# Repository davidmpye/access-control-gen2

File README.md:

This repo contains the Controllers (firmware, pcb design, printables) that make up part of the Makerspace Access Control System.

The basic principles they follow are:

* Use NFC readers (enrol a fob or card of your choice)
* Receive updates over Wifi, but cached on the controller in flash storage.
* Able to work offline and queue events to send to controller when connectivity established
* Provide log updates to the access controller backend to allow device usage to be logged and tracked.

They're an important part of our Health and Safety obligations to our members, ensuring that only authorised users are able to use (potentially) dangerous hardware.

The documentation is on the [wiki (in progress...!)](https://github.com/MakerSpaceNewcastle/access-control-gen2/wiki)

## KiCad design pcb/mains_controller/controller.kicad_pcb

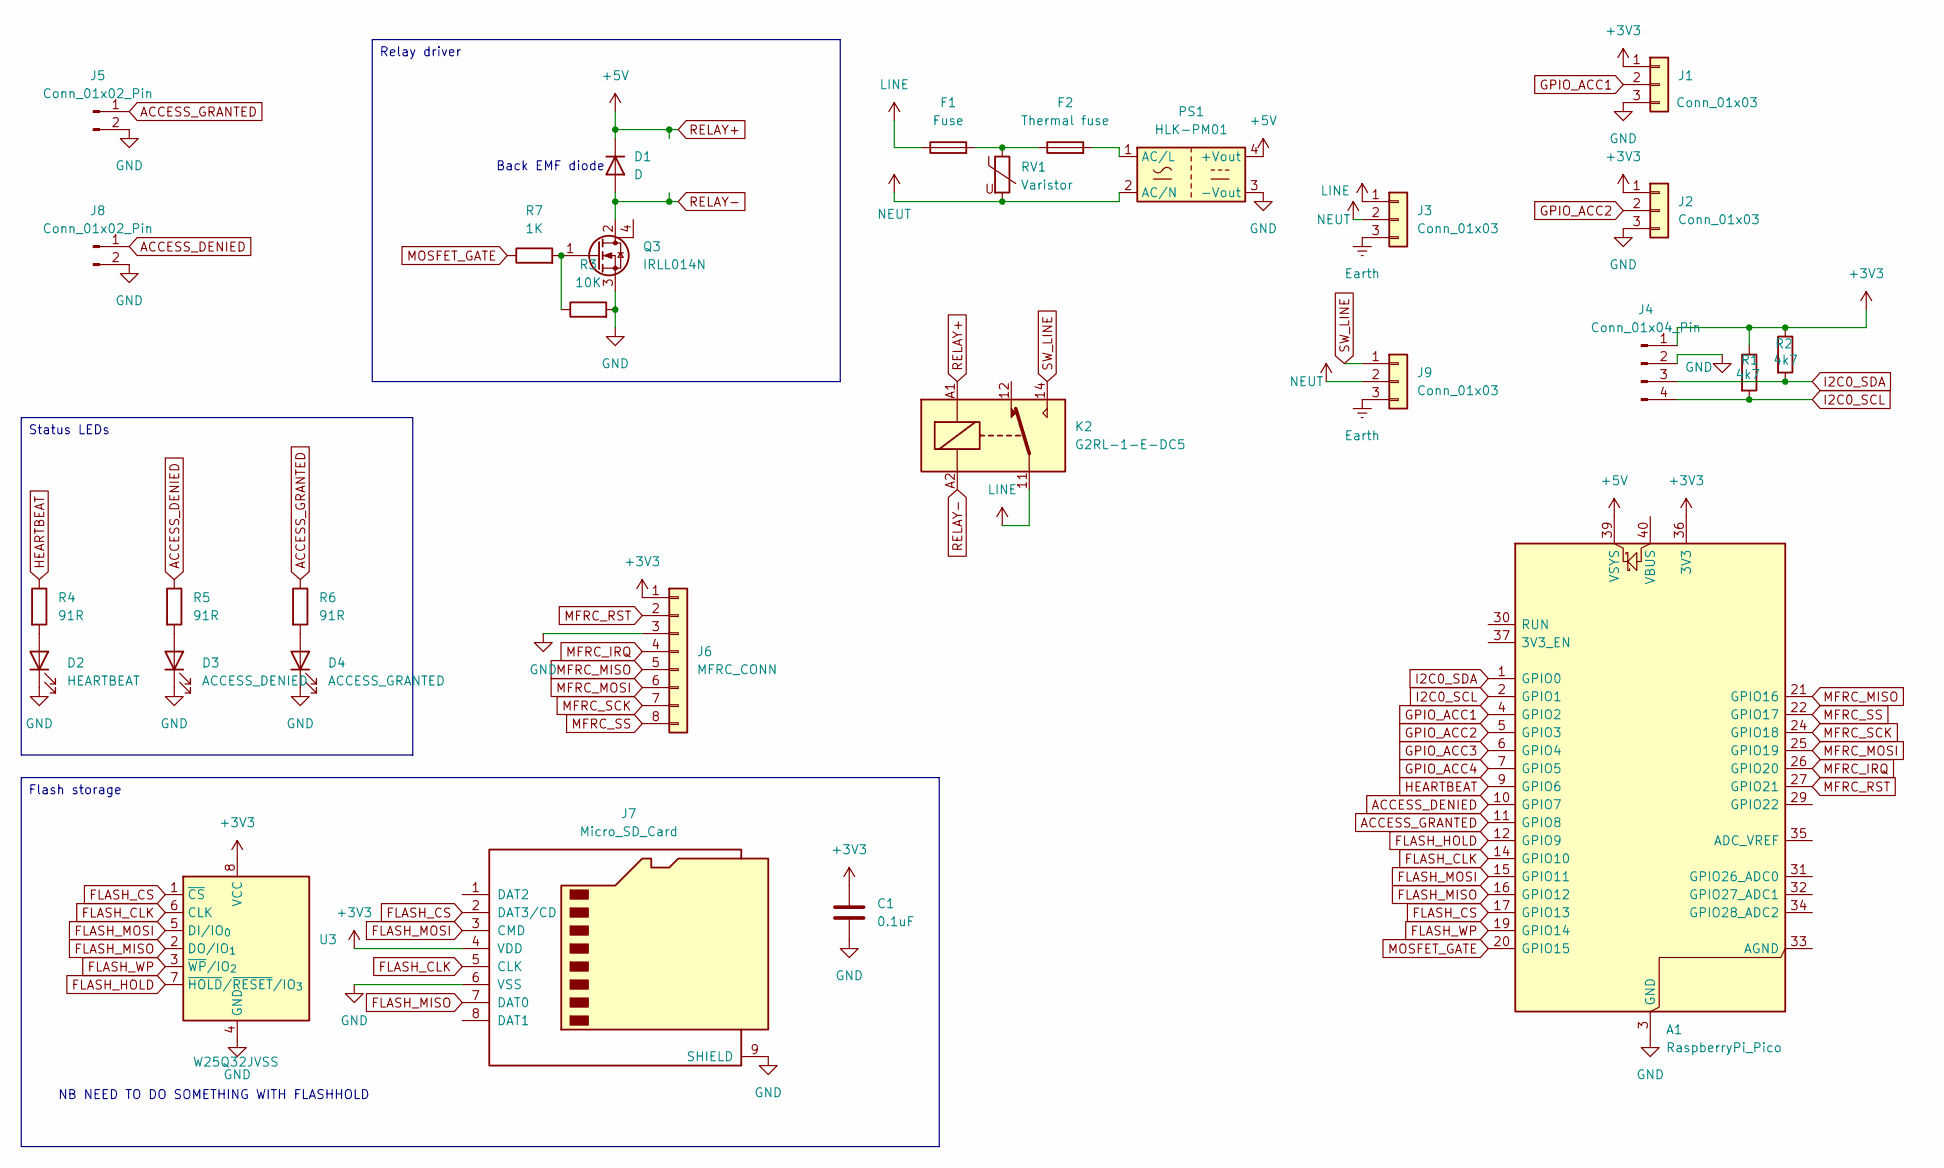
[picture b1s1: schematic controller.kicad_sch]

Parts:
A1: RaspberryPi_Pico; RaspberryPi_Pico_SMD_HandSolder
C1: 0.1uF; C_1206_3216Metric_Pad1.33x1.80mm_HandSolder
D1: D; D_SMA-SMB_Universal_Handsoldering
D2: HEARTBEAT; LED_1206_3216Metric_Pad1.42x1.75mm_HandSolder
D3: ACCESS_DENIED; LED_1206_3216Metric_Pad1.42x1.75mm_HandSolder
D4: ACCESS_GRANTED; LED_1206_3216Metric_Pad1.42x1.75mm_HandSolder
F1: Fuse; Fuseholder_Clip-5x20mm_Keystone_3517_Inline_P23.11x6.76mm_D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; Digikey PN 36-3517-ND
F2: Thermal fuse; R_Axial_DIN0204_L3.6mm_D1.6mm_P5.08mm_Horizontal
J1, J2: Conn_01x03; JST_XH_B3B-XH-A_1x03_P2.50mm_Vertical
J3: Conn_01x03; TerminalBlock_MetzConnect_Type073_RT02603HBLU_1x03_P5.08mm_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; Digikey PN 609-3937-ND
J4: Conn_01x04_Pin; JST_XH_B4B-XH-A_1x04_P2.50mm_Vertical
J5, J8: Conn_01x02_Pin; JST_XH_B2B-XH-A_1x02_P2.50mm_Vertical
J6: MFRC_CONN; PinHeader_1x08_P2.54mm_Vertical
J7: Micro_SD_Card; microSD_HC_Molex_104031-0811
J9: Conn_01x03; TerminalBlock_MetzConnect_Type073_RT02603HBLU_1x03_P5.08mm_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
K2: G2RL-1-E-DC5; Relay_SPDT_Omron_G2RL-1-E; Digikey Z2824-ND
PS1: HLK-PM01; Converter_ACDC_Hi-Link_HLK-PMxx
Q3: IRLL014N; SOT-223-3_TabPin2
R1, R2: 4k7; R_1210_3225Metric_Pad1.30x2.65mm_HandSolder
R3: 10K; R_1210_3225Metric_Pad1.30x2.65mm_HandSolder
R4, R5, R6: 91R; R_1210_3225Metric_Pad1.30x2.65mm_HandSolder
R7: 1K; R_1210_3225Metric_Pad1.30x2.65mm_HandSolder
RV1: Varistor; RV_Disc_D7mm_W4.9mm_P5mm; Digikey PN 118-MOV-07D301KTR
U3: W25Q32JVSS; SOIC-8_5.3x5.3mm_P1.27mm

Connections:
+3V3: A1.36 (3V3), C1.1, J1.1, J2.1, J4.1, J6.1, J7.4 (VDD), R1.1, R2.1, U3.8 (VCC)
ACCESS_DENIED: A1.10 (GPIO7), J8.1, R5.1
ACCESS_GRANTED: A1.11 (GPIO8), J5.1, R6.1
Earth: J3.3, J9.3
FLASH_CLK: A1.14 (GPIO10), J7.5 (CLK), U3.6 (CLK)
FLASH_CS: A1.17 (GPIO13), J7.2 (DAT3/CD), U3.1 (~CS)
FLASH_HOLD: A1.12 (GPIO9), U3.7 (~HOLD/~RESET/IO_{3})
FLASH_MISO: A1.16 (GPIO12), J7.7 (DAT0), U3.2 (DO/IO_{1})
FLASH_MOSI: A1.15 (GPIO11), J7.3 (CMD), U3.5 (DI/IO_{0})
FLASH_WP: A1.19 (GPIO14), U3.3 (~WP/IO_{2})
GND: A1.3 (GND), A1.8 (GND), A1.13 (GND), A1.18 (GND), A1.23 (GND), A1.28 (GND), A1.38 (GND), C1.2, D2.1 (K), D3.1 (K), D4.1 (K), J1.3, J2.3, J4.2, J5.2, J6.3, J7.6 (VSS), J7.9 (SHIELD), J8.2, PS1.3 (-Vout), Q3.3 (S), R3.2, U3.4 (GND)
GPIO_ACC1: A1.4 (GPIO2), J1.2
GPIO_ACC2: A1.5 (GPIO3), J2.2
GPIO_ACC3: A1.6 (GPIO4)
GPIO_ACC4: A1.7 (GPIO5)
HEARTBEAT: A1.9 (GPIO6), R4.1
I2C0_SCL: A1.2 (GPIO1), J4.4, R1.2
I2C0_SDA: A1.1 (GPIO0), J4.3, R2.2
LINE: F1.1, J3.1, K2.11
MFRC_IRQ: A1.26 (GPIO20), J6.4
MFRC_MISO: A1.21 (GPIO16), J6.5
MFRC_MOSI: A1.25 (GPIO19), J6.6
MFRC_RST: A1.27 (GPIO21), J6.2
MFRC_SCK: A1.24 (GPIO18), J6.7
MFRC_SS: A1.22 (GPIO17), J6.8
MOSFET_GATE: A1.20 (GPIO15), R7.1
NEUT: J3.2, J9.2, PS1.2 (AC/N), RV1.2
unnamed: D2.2 (A), R4.2
unnamed: D3.2 (A), R5.2
unnamed: D4.2 (A), R6.2
unnamed: F1.2, F2.1, RV1.1
unnamed: F2.2, PS1.1 (AC/L)
unnamed: Q3.1 (G), R3.1, R7.2
RELAY+: A1.39 (VSYS), D1.1 (K), K2.A1, PS1.4 (+Vout)
RELAY-: D1.2 (A), K2.A2, Q3.2 (D)
SW_LINE: J9.1, K2.14

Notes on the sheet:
NB NEED TO DO SOMETHING WITH FLASHHOLD
Back EMF diode
Status LEDs
Relay driver
Flash storage

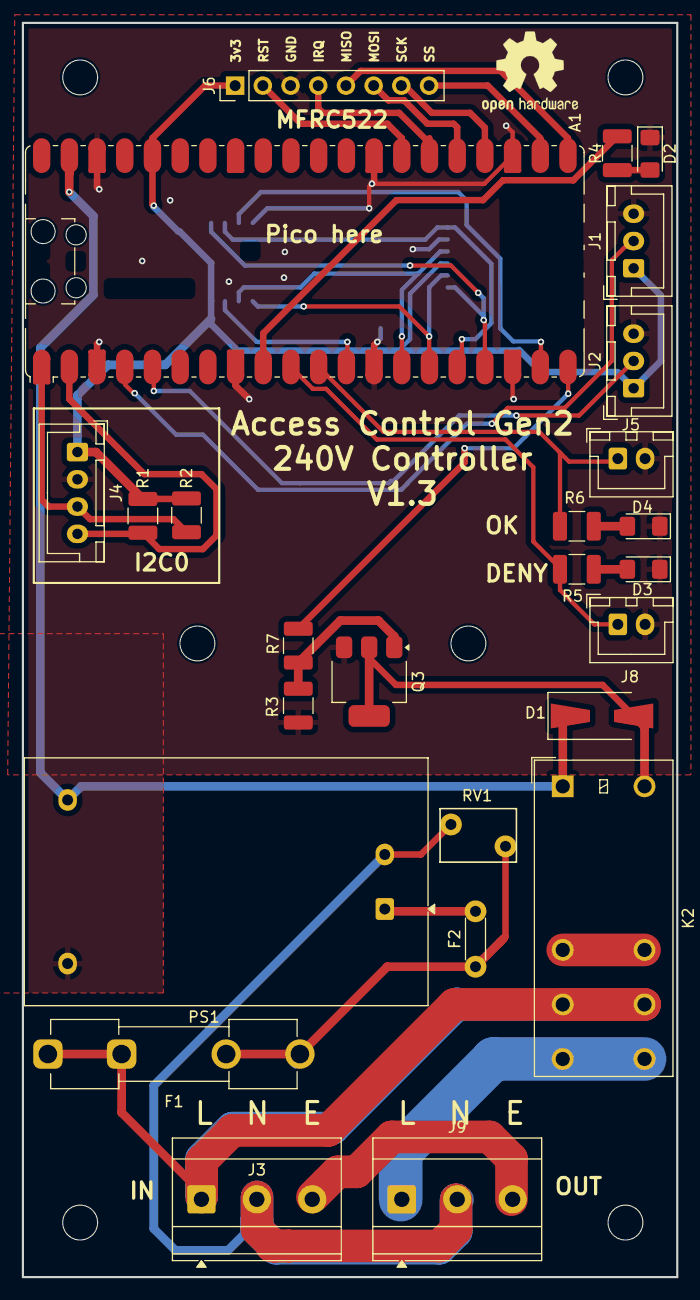
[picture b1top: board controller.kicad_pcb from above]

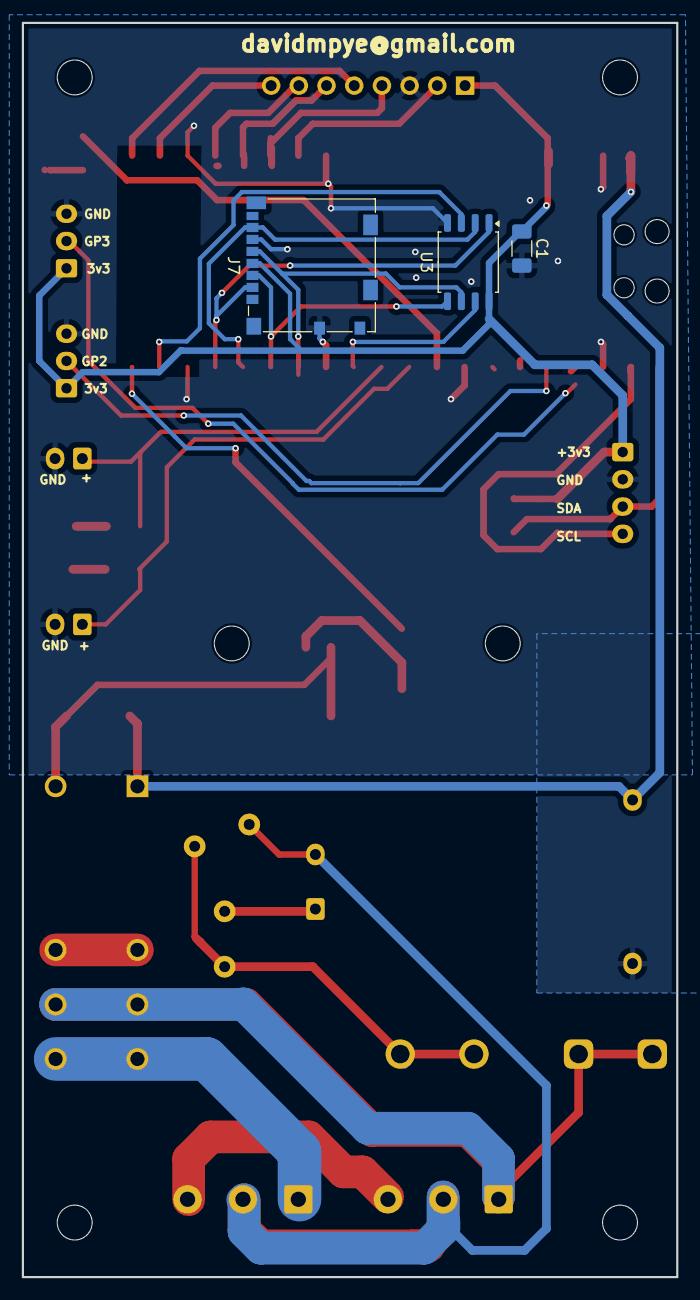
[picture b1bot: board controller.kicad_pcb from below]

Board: 2 copper layers, 60.0 x 115.0 mm, 29 parts (3 on the bottom side), 34 nets.

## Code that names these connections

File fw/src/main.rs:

#![no_std]
#![no_main]
#![allow(async_fn_in_trait)]

use cyw43::JoinOptions;
use cyw43_pio::{PioSpi, DEFAULT_CLOCK_DIVIDER};

use embedded_hal::digital::OutputPin;
//For SPI flash
use w25q32jv::W25q32jv;

use defmt::*;

use {defmt_rtt as _, panic_probe as _};

use embassy_executor::Spawner;
use embassy_net::{Config as WifiConfig, StackResources};
use embassy_rp::bind_interrupts;
use embassy_rp::clocks::RoscRng;
use embassy_rp::gpio::{Level, Output};
use embassy_rp::peripherals::{DMA_CH0, PIO0, UART0};
use embassy_rp::pio::{InterruptHandler, Pio};
use embassy_rp::spi::{Config as SpiConfig, Spi};
use embassy_rp::uart::{Config as UartConfig, InterruptHandler as UartInterruptHandler, Uart};
use embassy_time::{Delay, Timer};

use embedded_hal_bus::spi::{ExclusiveDevice, NoDelay};

use static_cell::StaticCell;

use rand::RngCore;

mod database_task;
mod local_cardreader_task;
mod log_task;
mod main_task;
mod remote_cardreader_task;
mod watchdog;

use database_task::DatabaseRunner;
use local_cardreader_task::LocalCardreaderTaskRunner;
use main_task::main_task;
use remote_cardreader_task::remote_cardreader_task;
use watchdog::watchdog_task;

use log_task::{LogEvent, LogTaskRunner, LOG_EVENT_QUEUE};
mod config;
use config::CONFIG;

bind_interrupts!(struct Irqs {
    PIO0_IRQ_0 => InterruptHandler<PIO0>;
    UART0_IRQ => UartInterruptHandler<UART0>;
});

#[embassy_executor::task]
async fn cyw43_task(
    runner: cyw43::Runner<'static, Output<'static>, PioSpi<'static, PIO0, 0, DMA_CH0>>,
) -> ! {
    runner.run().await
}

#[embassy_executor::task]
async fn net_task(mut runner: embassy_net::Runner<'static, cyw43::NetDriver<'static>>) -> ! {
    runner.run().await
}

#[embassy_executor::task]
async fn database_task(
    runner: DatabaseRunner<
        W25q32jv<
            ExclusiveDevice<
                Spi<'static, embassy_rp::peripherals::SPI1, embassy_rp::spi::Blocking>,
                Output<'static>,
                NoDelay,
            >,
            Output<'static>,
            Output<'static>,
        >,
    >,
) -> ! {
    runner.run().await
}

#[embassy_executor::task]
async fn log_task(runner: LogTaskRunner) -> ! {
    runner.run().await
}

#[embassy_executor::task]
async fn local_cardreader_task(
    mut runner: LocalCardreaderTaskRunner<
        ExclusiveDevice<
            Spi<'static, embassy_rp::peripherals::SPI0, embassy_rp::spi::Blocking>,
            Output<'static>,
            Delay,
        >,
        Output<'static>,
    >,
) -> ! {
    runner.run().await
}

#[embassy_executor::main]
async fn main(spawner: Spawner) {
    let p = embassy_rp::init(Default::default());

    //Spawn the watchdog task
    spawner.must_spawn(watchdog_task(p.WATCHDOG, Output::new(p.PIN_6, Level::High)));

    let pwr = Output::new(p.PIN_23, Level::Low);
    let cs = Output::new(p.PIN_25, Level::High);
    let mut pio = Pio::new(p.PIO0, Irqs);
    let spi = PioSpi::new(
        &mut pio.common,
        pio.sm0,
        DEFAULT_CLOCK_DIVIDER,
        pio.irq0,
        cs,
        p.PIN_24,
        p.PIN_29,
        p.DMA_CH0,
    );

    //Set up SPI1 for the flash memory storage
    let (sck, mosi, miso, cs) = (p.PIN_10, p.PIN_11, p.PIN_12, &p.PIN_13);
    let spi1: Spi<'_, embassy_rp::peripherals::SPI1, embassy_rp::spi::Blocking> =
        Spi::new_blocking(p.SPI1, sck, mosi, miso, SpiConfig::default());
    let flash_wp = Output::new(p.PIN_14, Level::Low); //WP is ACTIVE LOW - start with flash WP set
    let flash_hold = Output::new(p.PIN_9, Level::High); //Flash hold is ACTIVE LOW - start with hold not enabled
    let flash_cs = Output::new(p.PIN_13, Level::High); //SPI flash CS pin
    let spi_device = embedded_hal_bus::spi::ExclusiveDevice::new_no_delay(spi1, flash_cs);
    let mut spi_flash =
        W25q32jv::new(spi_device, flash_hold, flash_wp).expect("Unable to initialise flash");
    info!(
        "SPI flash (W25Q32) initialised - device id {}",
        spi_flash.device_id().expect("Unable to read flash ID")
    );

    //Wifi hardware setup
    static STATE: StaticCell<cyw43::State> = StaticCell::new();
    let fw = include_bytes!("../cyw43-firmware/43439A0.bin");
    let clm = include_bytes!("../cyw43-firmware/43439A0_clm.bin");
    let state = STATE.init(cyw43::State::new());
    let (net_device, mut control, runner) = cyw43::new(state, pwr, spi, fw).await;
    unwrap!(spawner.spawn(cyw43_task(runner)));

    control.init(clm).await;
    control
        .set_power_management(cyw43::PowerManagementMode::PowerSave)
        .await;

    // Init network stack
    let config = WifiConfig::dhcpv4(Default::default());
    let mut rng = RoscRng;
    let seed = rng.next_u64();
    static RESOURCES: StaticCell<StackResources<5>> = StaticCell::new();
    let (stack, runner) = embassy_net::new(
        net_device,
        config,
        RESOURCES.init(StackResources::new()),
        seed,
    );
    //Spawn network task
    unwrap!(spawner.spawn(net_task(runner)));

    //Set up channel to receive card hash
    //Set up the appropriate task to read from the card reader - either local (direct SPI) or remote (via RS485 link)
    if cfg!(not(feature = "remote-cardreader")) {
        info!("Local cardreader mode selected");
        //Local task - will poll SPI cardreader over local bus
        let (sck, mosi, miso, cs) = (p.PIN_18, p.PIN_19, p.PIN_16, p.PIN_17);
        let spi0 = Spi::new_blocking(p.SPI0, sck, mosi, miso, SpiConfig::default());
        let spi0: ExclusiveDevice<
            Spi<'_, embassy_rp::peripherals::SPI0, embassy_rp::spi::Blocking>,
            Output,
            Delay,
        > = ExclusiveDevice::new(spi0, Output::new(cs, Level::High), Delay);
        debug!("Spawning local card reader task");
        spawner.must_spawn(local_cardreader_task(LocalCardreaderTaskRunner::new(
            spi0,
            Output::new(p.PIN_21, Level::High),
        )));
    } else {
        //Remote task
        info!("Remote cardreader mode selected");
        let (tx_pin, rx_pin, uart) = (p.PIN_0, p.PIN_1, p.UART0);
        let uart = Uart::new(
            uart,
            tx_pin,
            rx_pin,
            Irqs,
            p.DMA_CH2,
            p.DMA_CH3,
            UartConfig::default(),
        );
        debug!("Spawning remote card reader task");
        spawner.must_spawn(remote_cardreader_task(uart));
    }

    //Spawn the main task
    let allowed = Output::new(p.PIN_7, Level::Low);
    let denied = Output::new(p.PIN_8, Level::Low);
    let relay_pin = Output::new(p.PIN_15, Level::Low);
    spawner.must_spawn(main_task(relay_pin, allowed, denied));

    //Spawn the database task
    spawner.must_spawn(database_task(DatabaseRunner::new(
        spi_flash,
        2 * 1024 * 1024, //2mbit
        0x00,
        stack,
    )));

    //Spawn the logger task
    spawner.must_spawn(log_task(LogTaskRunner::new(stack)));

    loop {
        match control
            .join(CONFIG.ssid, JoinOptions::new(CONFIG.wifi_pw.as_bytes()))
            .await
        {
            Ok(_) => {
                info!("WiFi network {} joined, configuring stack", CONFIG.ssid);
                break;
            }
            Err(err) => {
                error!(
                    "Failed to join {}, status {}, retrying in 10s",
                    CONFIG.ssid, err.status
                );
                Timer::after_secs(10).await;
            }
        }
    }

    //Complete init of Wifi stack
    debug!("DHCP init");
    stack.wait_config_up().await;
    debug!("Config ready, awaiting link up");
    stack.wait_link_up().await;
    debug!("Link ready, awaiting config up");
    stack.wait_config_up().await;
    info!("Wifi ready");
    //Main function is now complete - the peripherals/tasks/stack are operational
}

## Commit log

2025-06-07 Initial import of fw
2025-06-07 Add gitignore for /target
2025-06-07 Fix build infra
2025-06-07 Update Cargo
2025-06-07 Further build infra
2025-06-07 Initial import of fw draft
2025-06-08 Add the CYW43 firmware
2025-06-08 Re-add main
2025-07-20 Modify the remote unit fw to use cobs
2025-07-30 Add remote cardreader as separate task
2025-07-31 Change card reader message enums and add in regular 'OK' messages in the absence of a card read, so we can tell if the remote unit is online
2025-07-31 More refactoring, rename KeepAlive message
2025-07-31 Restructure byte read loop
2025-07-31 Adjust message
2025-07-31 Rename buffer overflow
2025-08-02 Initial import of the kicad project for the controller. Update some of the rust project libraries
2025-08-04 Start feature work for remote/local mfrc522
2025-08-04 cargo updates
2025-08-14 Initial flash code test
2025-08-18 Separate out logic into database task for flash updates/sync
2025-11-11 Footprint updates Major restructuring
2025-11-12 Add http timeout
2025-11-12 Update to use Duration as Latchmode
2025-11-12 Main updates
2025-11-12 Update executor task space
2025-11-12 Config.rs template
2025-11-13 Change from using Signal to Channel for logger, to allow up to 32 log events to be queued for sending (eg if wifi unavailable)
2025-11-13 Changes to event logger logic
2025-11-13 Allow main task to finish, rather than sit in await loop Change debug!/info! levels to reduce chatter
2025-11-13 Add timeout functionality to logger
2025-11-13 Increase task arena size (again!)
2025-11-13 Used 'format document' to adjust formatting. Shorten message queue length from 32->16 events
2025-11-13 Main task now holds the hash of the logged in user, and will send this back to confirm *who* logged out, regardless of what signout card was used
2025-11-14 Change MD5 hash handling
2025-11-14 Reduce info! level noise -> debug!
2025-11-14 Rearrange order of task init in main(), including starting the watchdog earlier
2025-11-14 Push timeout into main database task loop
2025-11-14 Further push-up of timeout
2025-11-14 Reorder use statements
2025-11-14 Reinstate log timeouts
2025-11-14 Stop log task spamming if a connection fails
2025-11-15 Tidy logger logic and reformat some defmt messages
2025-11-15 Update log task to impl defmt::Format for errors
2025-11-16 Use format trait, and thus rationalise use of defmt macros
2025-11-17 Break out database functions more sensibly
2025-11-19 Cargo update 'd
2025-11-23 More updates
2025-11-23 Improve local
2025-11-23 Tweak error msg
2025-11-23 Fix wupa logic
2025-11-23 Move cardreader event signal into main_task
2025-11-23 Refactor/renames
2025-11-23 Change if let to match
2025-11-24 Improve remote cardreader logic by using copy_from_slice
2025-11-25 Change the default feature to 'local' cardreader.
2025-11-27 PCB changes - add GPIO3/4
2025-11-27 Minor silkscreen changes
2025-11-27 Add mains controller branch
2025-11-29 Add printables
2025-11-29 Add SCAD readme
2025-11-29 Rename + add readme
2025-11-29 Start design for mains controller
2025-11-30 Production version (sent to JLC!)
2025-12-01 Add digikey PNs
2025-12-01 Restructure project directories and break out the uart_protocol into separate crate
2025-12-01 Complete migration to uart_protocol crate
2025-12-01 Add readme
2025-12-01 Add the uart_protocol bits
2025-12-01 Implementation of remote LED functionality
2025-12-02 Fix rust version to 2021 in uart protocol
2025-12-02 Add remote cardreader LED control messages
2025-12-02 Add signals for remote cardreader (fixme - only use signal if remote device present
2025-12-02 Add embassy_futures and update debug comments
2025-12-02 Use #derive debug/format for logerror use pub(crate) more
2025-12-02 More pub(crate) and derive debug/formats
2025-12-02 Use map_err(_) rather than Into
2025-12-02 Another map_error and unnecessary mut
2025-12-02 Update Cargo.toml + README for protocol
2025-12-03 Change logic for LED (GPIO pull to low) Brief flash on power up
2025-12-03 Add comment re hanging
2025-12-14 Add delay after successful read to prevent immediately logging out
2025-12-14 Flip LEDs
2025-12-14 Change 2sec pause
2025-12-14 Add hw
2025-12-14 Add insulator washer
2025-12-14 Update to 3
2025-12-14 Reposition securing holes for mfrc522 Make hole sizes bigger for varistor and thermal fuse Bump ver to 1.3
2025-12-14 Update filled areas
2025-12-14 Add stl in case you don't like openscad
2025-12-20 Add mains controller mounting brackets
2025-12-20 Add more vars
2025-12-20 Refactoring to use assign_resources and move peripheral initialisation into the tasks
2025-12-20 Update formatting
2025-12-20 Re-add blank config.rs
2025-12-20 Remove unneeded includes
2025-12-20 Flip LEDs back!
2025-12-20 Fix LED labelling again
2025-12-20 Formatting
2025-12-20 Add gitignore
2025-12-20 Remove that
2025-12-21 Clippy lints
2025-12-21 Squash more clippy lints
2025-12-21 More lints
2025-12-21 Format fixes
2025-12-21 Format
2025-12-21 Reformat to remove log_task_runner and just spawn the log_task directly
2025-12-21 Rename led_resouces to status_led_resources
2025-12-21 Fixes for pcb
2025-12-21 Add dead code allow
2025-12-23 Return heartbeat led to original function Move resource setup to assign_resources macro to match 'main' code
2025-12-23 Reformat use statements
2025-12-24 Brief LED flash in main_task to prove functionality
2025-12-24 Update mainsbracket to have screw mounting pillars to prevent risk of screws protruding through case
2025-12-24 Re-do
2025-12-25 Change logic levels so LEDS start in correct state
2025-12-25 Add in additional GPIO logic for external status LEDs
2025-12-26 Update to taper the holes for the heat-push brass inserts and make them deeper to avoid melted plastic getting stuck in threads during insertion
